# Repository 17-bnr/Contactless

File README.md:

# Contactless
for Tokyo Tech Festival 2022

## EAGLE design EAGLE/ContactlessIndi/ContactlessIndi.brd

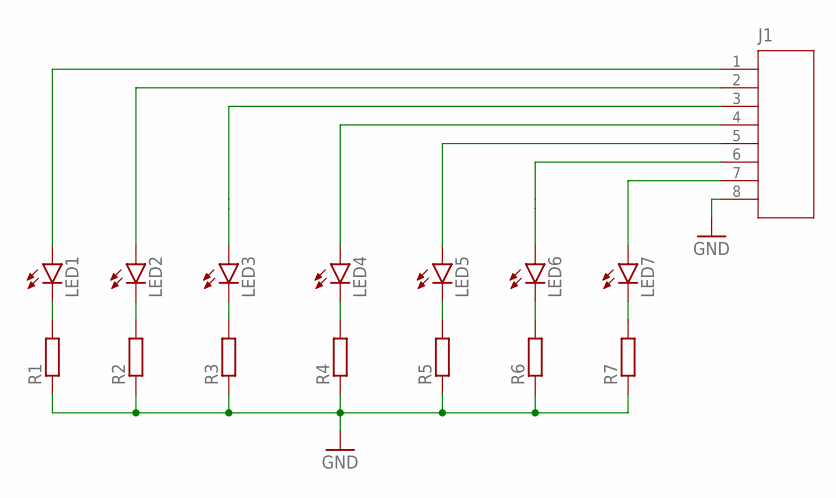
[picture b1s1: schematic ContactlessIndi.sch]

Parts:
J1: PINHEADER-818*1; PINHEADER-8*1
LED1, LED2, LED3, LED4, LED5, LED6, LED7: LED5MM
R1, R2, R3, R4, R5, R6, R7: R-EU_R1206; R1206

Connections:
GND: J1.8, R1.1, R2.1, R3.1, R4.1, R5.1, R6.1, R7.1
unnamed: LED1.K (C), R1.2
unnamed: LED2.K (C), R2.2
unnamed: LED3.K (C), R3.2
unnamed: LED4.K (C), R4.2
unnamed: LED5.K (C), R5.2
unnamed: LED6.K (C), R6.2
unnamed: LED7.K (C), R7.2
unnamed: J1.7, LED7.A
unnamed: J1.6, LED6.A
unnamed: J1.5, LED5.A
unnamed: J1.4, LED4.A
unnamed: J1.3, LED3.A
unnamed: J1.2, LED2.A
unnamed: J1.1, LED1.A

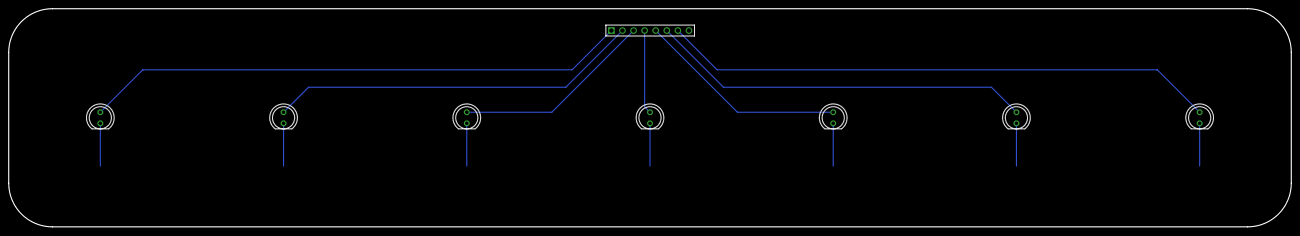
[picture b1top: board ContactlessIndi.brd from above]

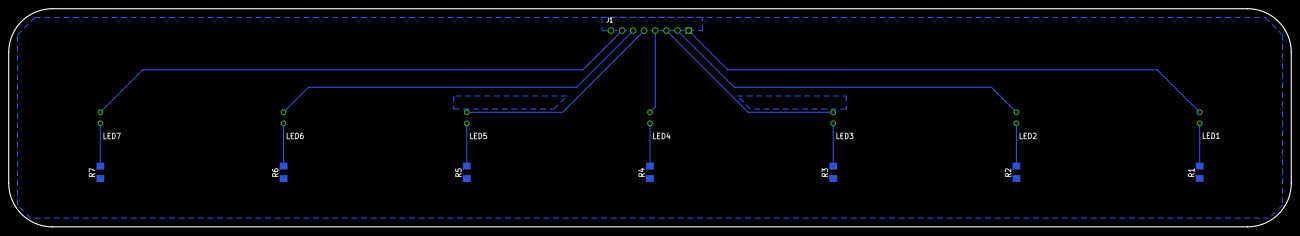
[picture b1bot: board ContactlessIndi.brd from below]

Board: 2 copper layers, 294.0 x 50.0 mm, 15 parts (7 on the bottom side), 15 nets.

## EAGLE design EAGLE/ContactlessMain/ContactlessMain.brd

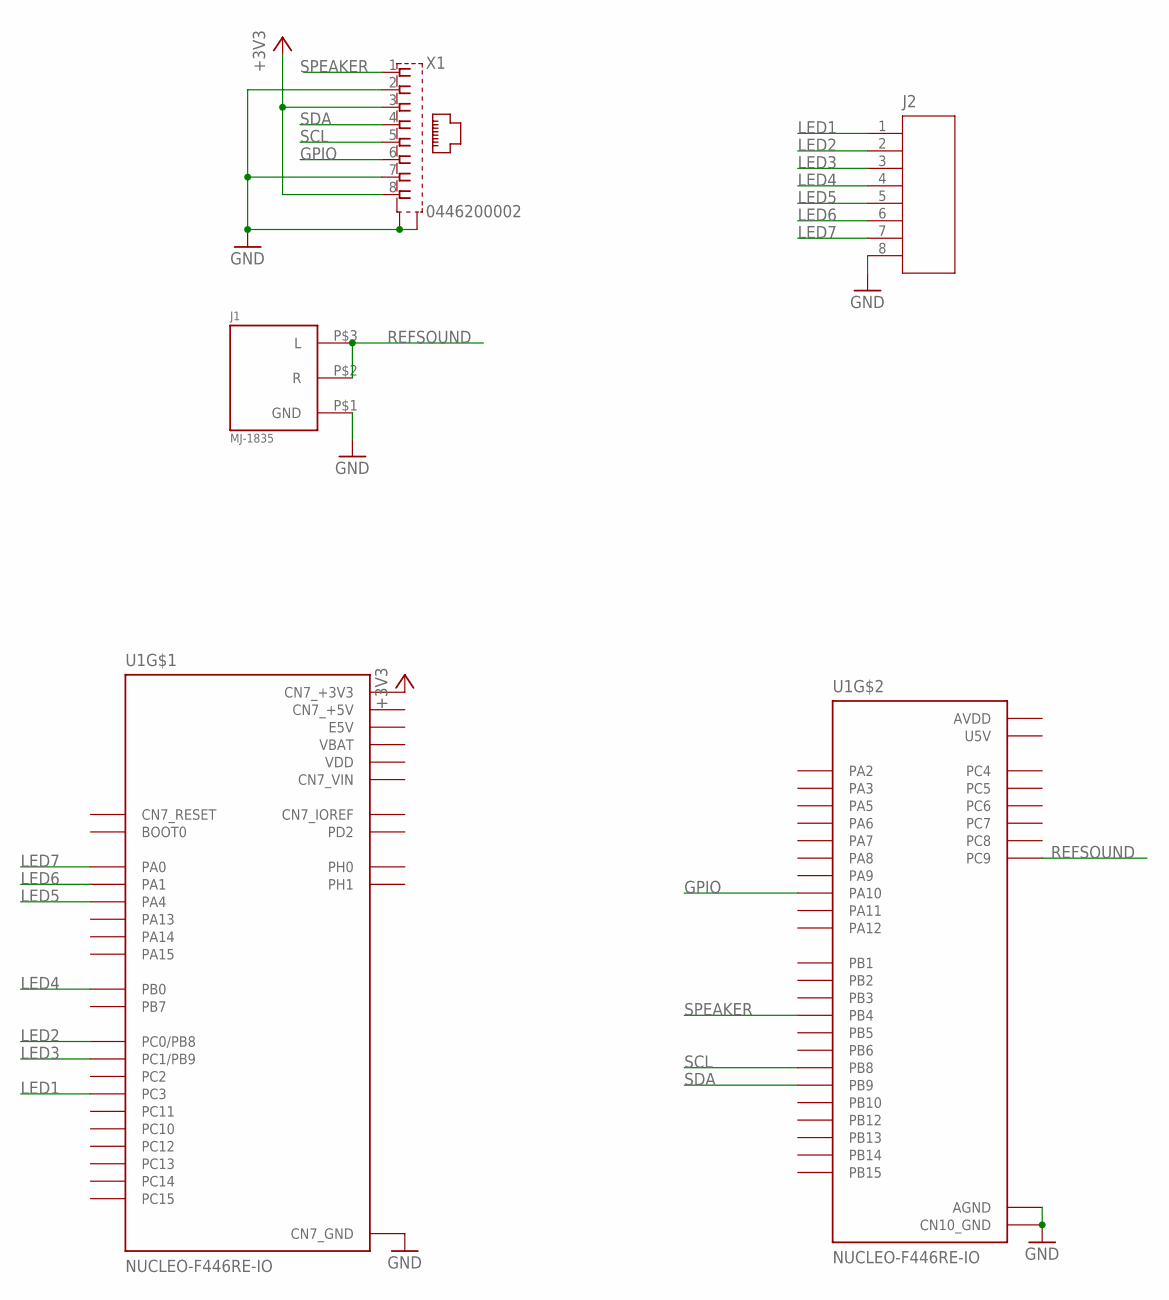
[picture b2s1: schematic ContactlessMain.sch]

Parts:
J1: MJ-1835
J2: PINHEADER-818*1; PINHEADER-8*1
U1: NUCLEO-F446RE-IO; MODULE_NUCLEO-F446RE
X1: 0446200002

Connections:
+3V3: U1.CN7_16 (CN7_+3V3), X1.3, X1.8
AVDD: U1.CN10_7 (AVDD)
CN7_+5V: U1.CN7_18 (CN7_+5V)
CN7_VIN: U1.CN7_24 (CN7_VIN)
E5V: U1.CN7_6 (E5V)
GND: J1.P$1 (GND), J2.8, U1.CN7_8 (CN7_GND), U1.CN7_19 (CN7_GND), U1.CN7_20 (CN7_GND), U1.CN7_22 (CN7_GND), U1.CN10_9 (CN10_GND), U1.CN10_20 (CN10_GND), U1.CN10_32 (AGND), X1.2, X1.7, X1.S@1 (S1), X1.S@2 (S2)
GPIO: U1.CN10_33 (PA10), X1.6
LED1: J2.1, U1.CN7_37 (PC3)
LED2: J2.2, U1.CN7_38 (PC0/PB8)
LED3: J2.3, U1.CN7_36 (PC1/PB9)
LED4: J2.4, U1.CN7_34 (PB0)
LED5: J2.5, U1.CN7_32 (PA4)
LED6: J2.6, U1.CN7_30 (PA1)
LED7: J2.7, U1.CN7_28 (PA0)
REFSOUND: J1.P$2 (R), J1.P$3 (L), U1.CN10_1 (PC9)
SCL: U1.CN10_3 (PB8), X1.5
SDA: U1.CN10_5 (PB9), X1.4
SPEAKER: U1.CN10_27 (PB4), X1.1
U5V: U1.CN10_8 (U5V)
VBAT: U1.CN7_33 (VBAT)
VDD: U1.CN7_5 (VDD)

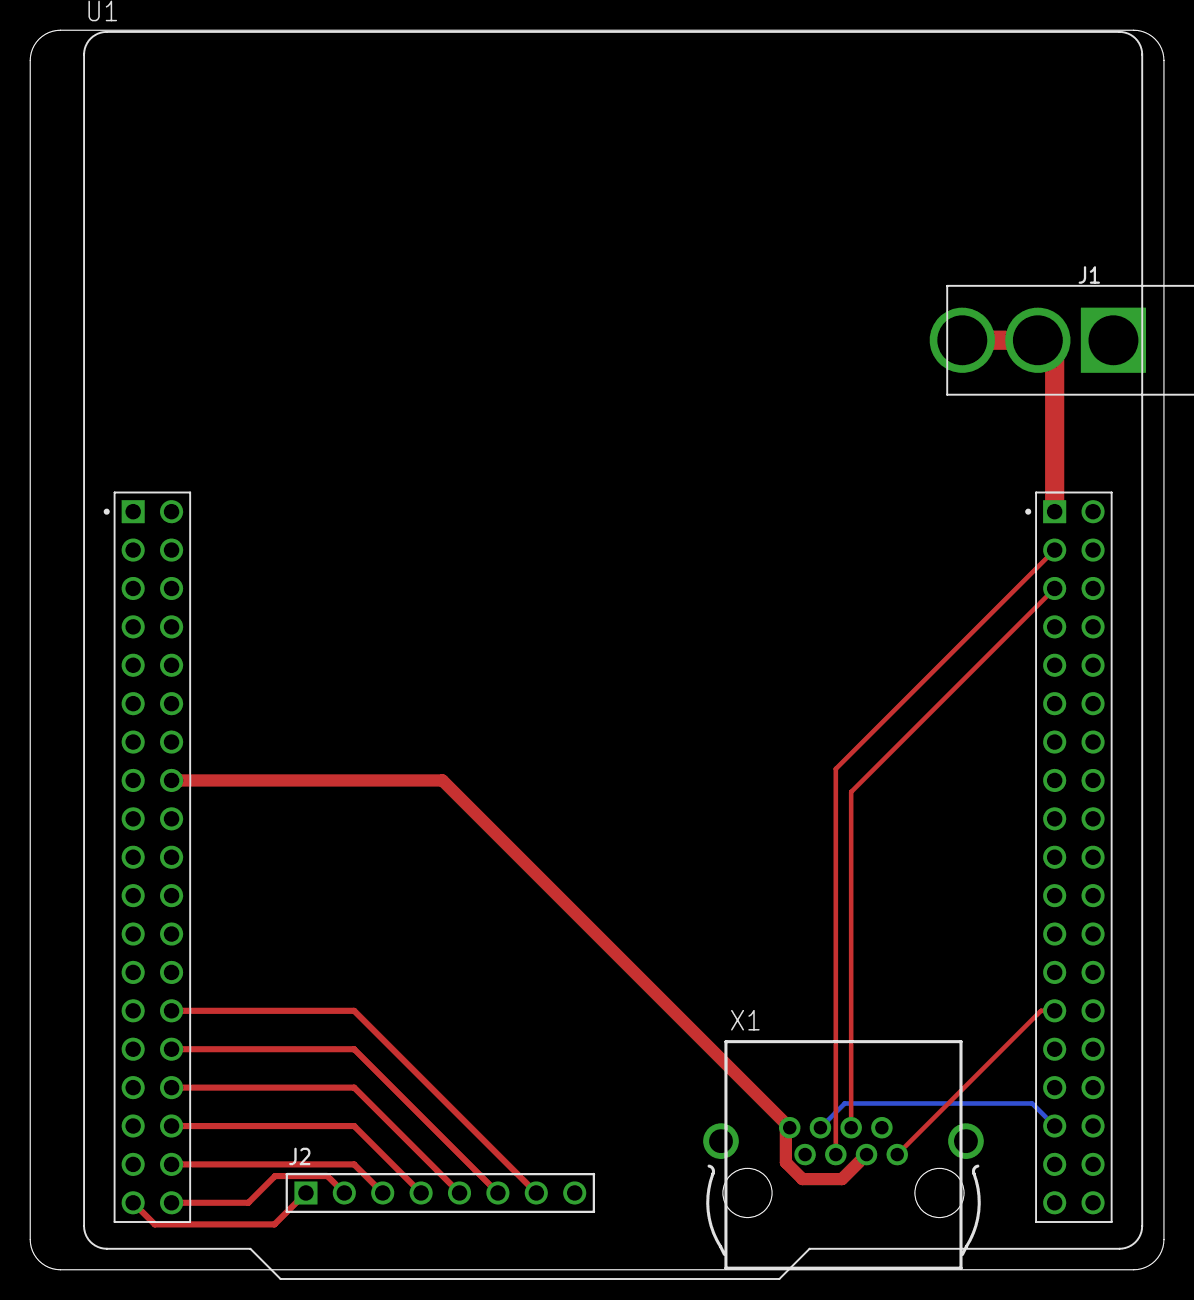
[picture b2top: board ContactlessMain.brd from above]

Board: 2 copper layers, 75.0 x 82.0 mm, 4 parts (0 on the bottom side), 14 nets.

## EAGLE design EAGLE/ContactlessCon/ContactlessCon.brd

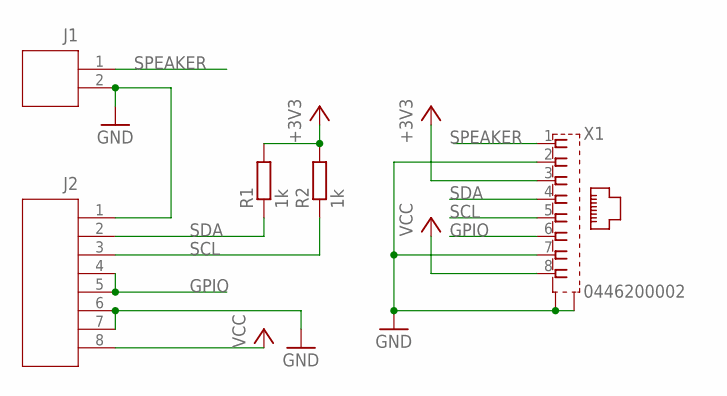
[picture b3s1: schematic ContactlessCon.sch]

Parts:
J1: PINHEADER-212*1; PINHEADER-2*1
J2: PINHEADER-818*1; PINHEADER-8*1
R1, R2: 1k; R1206
X1: 0446200002

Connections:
+3V3: R1.2, R2.2, X1.3
GND: J1.2, J2.1, J2.6, J2.7, X1.2, X1.7, X1.S@1 (S1), X1.S@2 (S2)
GPIO: J2.4, J2.5, X1.6
SCL: J2.3, R2.1, X1.5
SDA: J2.2, R1.1, X1.4
SPEAKER: J1.1, X1.1
VCC: J2.8, X1.8

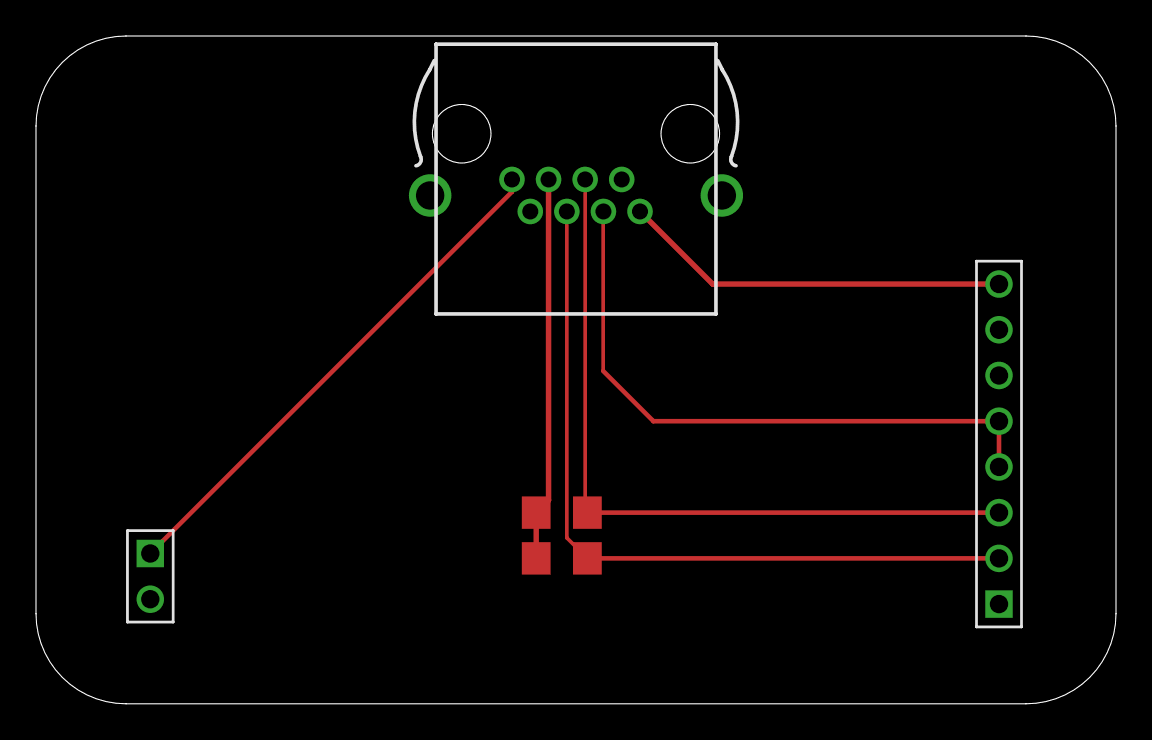
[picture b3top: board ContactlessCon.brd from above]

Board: 2 copper layers, 60.0 x 37.1 mm, 5 parts (0 on the bottom side), 7 nets.

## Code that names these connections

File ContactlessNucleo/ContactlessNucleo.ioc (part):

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Mcu.Name=STM32F446R(C-E)Tx
Mcu.Package=LQFP64
Mcu.UserName=STM32F446RETx
PA0-WKUP.GPIOParameters=GPIO_Label
PA0-WKUP.GPIO_Label=LED7
PA0-WKUP.Signal=GPIO_Output
PA1.GPIOParameters=GPIO_Label
PA1.GPIO_Label=LED6
PA1.Signal=GPIO_Output
PA10.GPIOParameters=GPIO_Label
PA10.GPIO_Label=GPIO
PA10.Signal=GPIO_Output
PA13.GPIOParameters=GPIO_Label
PA13.GPIO_Label=TMS
PA13.Mode=Serial_Wire
PA13.Signal=SYS_JTMS-SWDIO
PA14.GPIOParameters=GPIO_Label
PA14.GPIO_Label=TCK
PA14.Mode=Serial_Wire
PA14.Signal=SYS_JTCK-SWCLK
PA2.GPIOParameters=GPIO_Label
PA2.GPIO_Label=USART_TX
PA2.Mode=Asynchronous
PA2.Signal=USART2_TX
PA3.GPIOParameters=GPIO_Label
PA3.GPIO_Label=USART_RX
PA3.Mode=Asynchronous
PA3.Signal=USART2_RX
PA4.GPIOParameters=GPIO_Label
PA4.GPIO_Label=LED5
PA4.Signal=GPIO_Output
PA5.GPIOParameters=GPIO_Label
PA5.GPIO_Label=LD2 [Green Led]
PA5.Signal=GPIO_Output
PB0.GPIOParameters=GPIO_Label
PB0.GPIO_Label=LED4
PB0.Signal=GPIO_Output
PB3.GPIOParameters=GPIO_Label
PB3.GPIO_Label=SWO
PB3.Signal=SYS_JTDO-SWO
PB4.GPIOParameters=GPIO_Label
PB4.GPIO_Label=SPEAKER
PB4.Signal=S_TIM3_CH1
PB8.Mode=I2C
PB8.Signal=I2C1_SCL
PB9.Mode=I2C
PB9.Signal=I2C1_SDA
PC0.GPIOParameters=GPIO_Label
PC0.GPIO_Label=LED2
PC0.Signal=GPIO_Output
PC1.GPIOParameters=PinState,GPIO_Label
PC1.GPIO_Label=LED3
PC1.PinState=GPIO_PIN_RESET
PC1.Signal=GPIO_Output
PC13.GPIOParameters=GPIO_Label,GPIO_ModeDefaultEXTI
PC13.GPIO_Label=B1 [Blue PushButton]
PC13.GPIO_ModeDefaultEXTI=GPIO_MODE_IT_FALLING
PC13.Signal=GPXTI13
PC14-OSC32_IN.Mode=LSE-External-Oscillator
PC14-OSC32_IN.Signal=RCC_OSC32_IN
PC15-OSC32_OUT.Mode=LSE-External-Oscillator
PC15-OSC32_OUT.Signal=RCC_OSC32_OUT
PC3.GPIOParameters=GPIO_Label
PC3.GPIO_Label=LED1
PC3.Signal=GPIO_Output
PC9.GPIOParameters=GPIO_Label
PC9.GPIO_Label=REFSOUND
PC9.Signal=S_TIM8_CH4
PH0-OSC_IN.Mode=HSE-External-Oscillator
PH0-OSC_IN.Signal=RCC_OSC_IN
PH1-OSC_OUT.Mode=HSE-External-Oscillator
PH1-OSC_OUT.Signal=RCC_OSC_OUT
RCC.HSE_VALUE=8000000
RCC.SYSCLKFreq_VALUE=84000000
RCC.SYSCLKSource=RCC_SYSCLKSOURCE_PLLCLK
board=NUCLEO-F446RE
boardIOC=true

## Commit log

2022-09-15 edit README
2022-09-15 ToFセンサでI2Cできた
2022-09-15 SHARPセンサでI2Cできた
2022-09-17 PWMで2つの音を出力した
2022-09-19 距離センサの値で音階を変わるようにした
2022-10-08 LTspice追加
2022-10-08 EAGLEフォルダ作成
2022-10-08 回路図作成
2022-10-08 Conの配線終了
2022-10-09 抵抗のvalueを追加
2022-10-09 くっついてない電源を2つにわけてくっつけた
2022-10-09 Mainの回路図途中まで作成
2022-10-09 インジゲータ基板作成
2022-10-09 コントローラ基板のシルクをすべて裏にした
2022-10-09 Main基板の配線作成
2022-10-10 Main基板設計完了
2022-10-10 Gerber作成
2022-10-20 実機に合わせてピンアサインを変更
2022-10-20 機体設計ver1完了
2022-10-20 timer2内でDMAのI2C実装
2022-10-20 i2cのあとにgpioをinitし，timer2の周期を20Hzにした
2022-10-20 LEDと距離センサでstateを実装
2022-10-22 ASoundOn実装
2022-10-22 LED以外のstartは実装
2022-10-22 refactoring
2022-10-22 status全て完了
2022-10-23 LED実装
2022-10-24 側面の設計
2022-10-24 Daiの設計途中
2022-10-26 Dai下以外設計完了
2022-10-27 台の設計完了
2022-10-28 本日はありがとうございましたのポスター作成
2022-10-28 ポスター作成
2022-11-01 本番で判定の微調整
